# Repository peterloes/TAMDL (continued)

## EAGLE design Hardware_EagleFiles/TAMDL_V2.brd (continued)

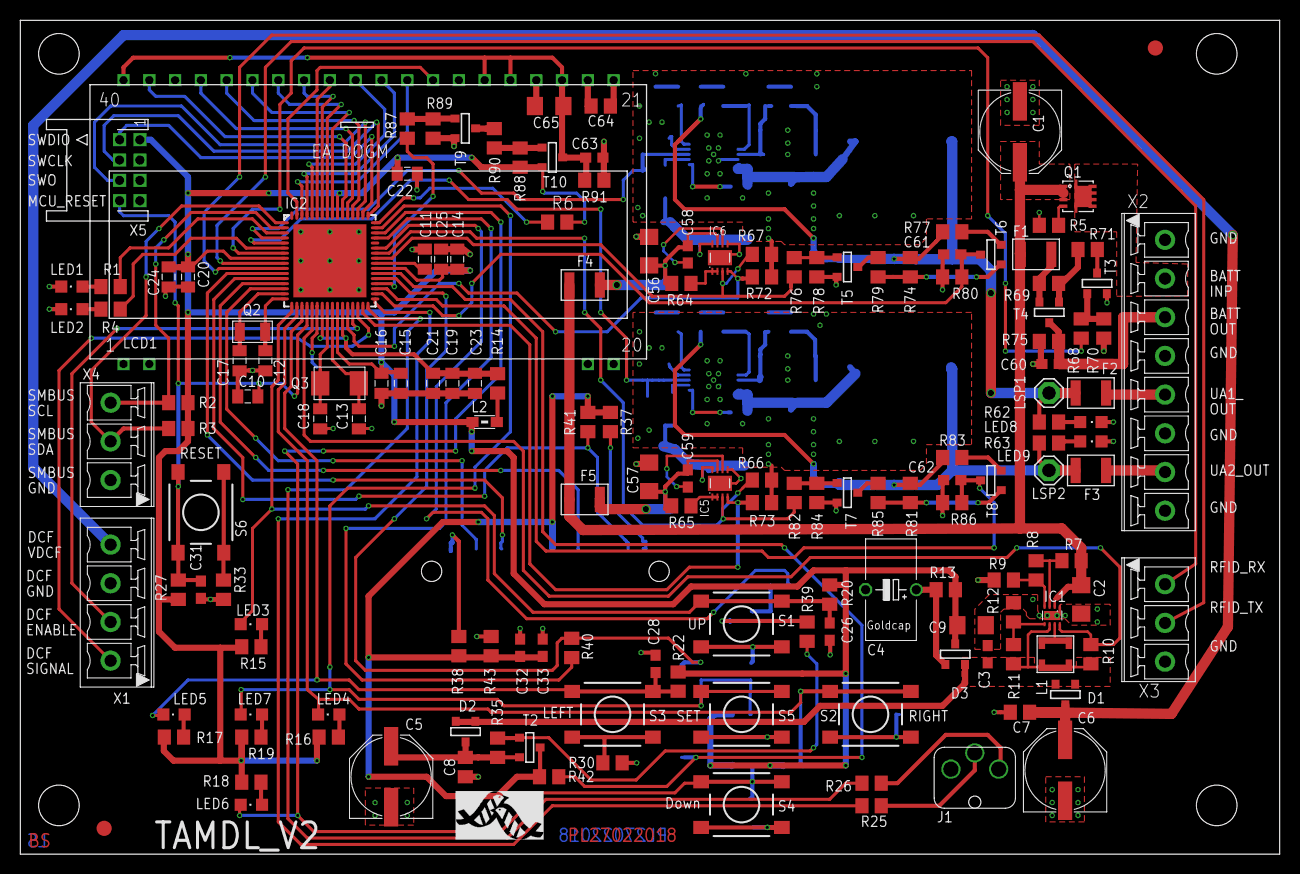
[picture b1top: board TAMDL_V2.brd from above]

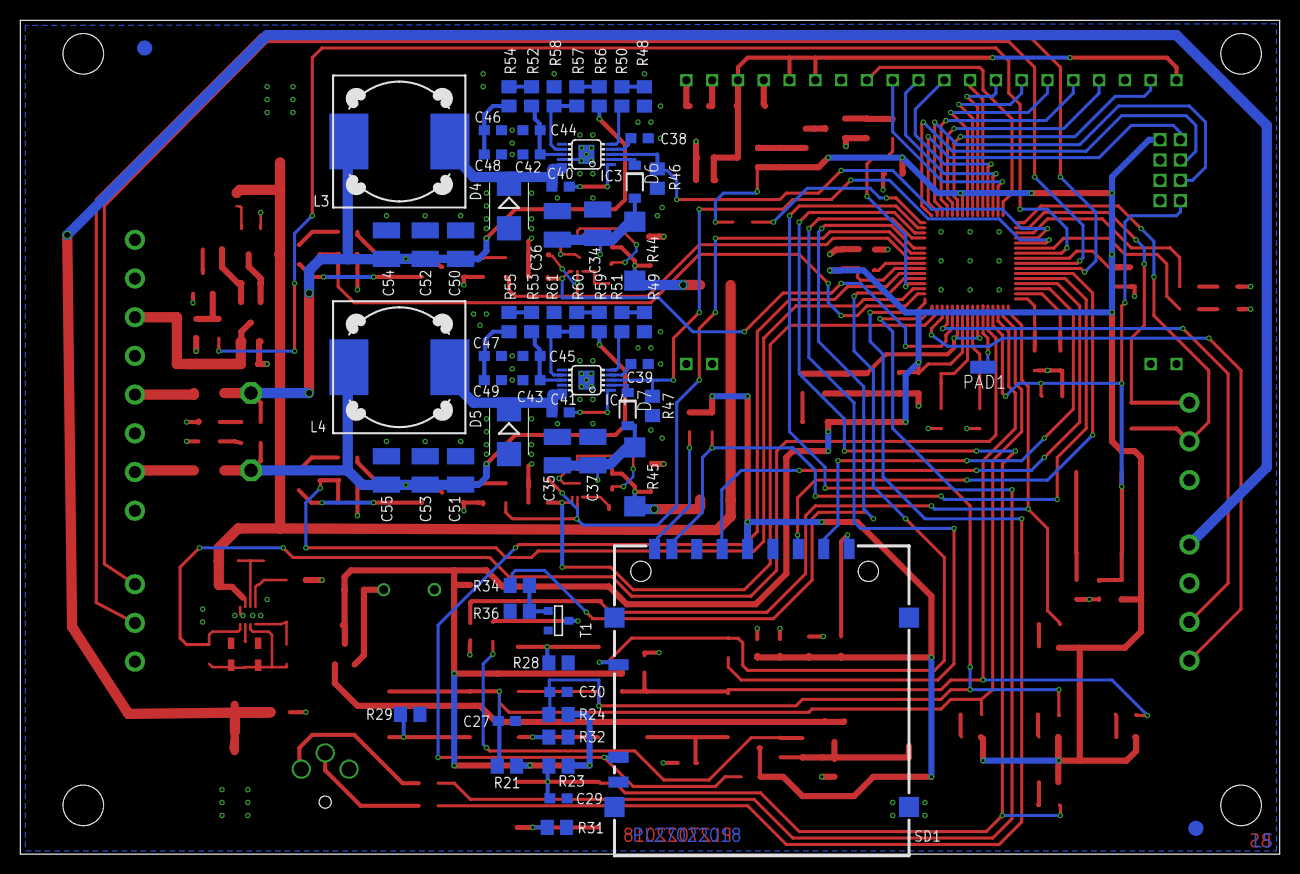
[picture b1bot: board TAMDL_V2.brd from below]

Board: 2 copper layers, 124.0 x 82.1 mm, 222 parts (65 on the bottom side), 148 nets.

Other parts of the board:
U$1: MPIO-ICON

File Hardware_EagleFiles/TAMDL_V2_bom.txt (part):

Part  Value                                             Device                  Package                Description                                                    MPN     OC_FARNELL OC_NEWARK PACKAGE  SUPPLIER         
C1    100µF/25V                                         CPOL-EUE                PANASONIC_E            POLARIZED CAPACITOR, European symbol                                                                                  
C2    10µF/25V                                          C-EUC1206               C1206                  CAPACITOR, European symbol                                                                                            
C3    22µF/10V                                          C-EUC0603               C0603                  CAPACITOR, European symbol                                                                                            
C4    EECS0HD 224;Panasonic                             GOLDCAPSPK-V            GOLDCAPSPK-V                                                                                                                                 
C5    100µF/25V                                         CPOL-EUE                PANASONIC_E            POLARIZED CAPACITOR, European symbol                                                                                  
C6    100µF/25V                                         CPOL-EUE                PANASONIC_E            POLARIZED CAPACITOR, European symbol                                                                                  
C7    100nF/16V                                         C-EUC0805               C0805                  CAPACITOR, European symbol                                                                                            
C8    100nF/16V                                         C-EUC0805               C0805                  CAPACITOR, European symbol                                                                                            
C9    10µ/25V                                           C-EUC1206               C1206                  CAPACITOR, European symbol                                                                                            
C10   100n                                              C_SMD0805               0805                                                                                                                                         
C11   1u                                                C_SMD0805               0805                                                                                                                                         
C12   18p                                               C_SMD0805               0805                                                                                                                                         
C13   12p                                               C_SMD0805               0805                                                                                                                                         
C14   100n                                              C_SMD0805               0805                                                                                                                                         
C15   100n                                              C_SMD0805               0805                                                                                                                                         
C16   100n                                              C_SMD0805               0805                                                                                                                                         
C17   18p                                               C_SMD0805               0805                                                                                                                                         
C18   12p                                               C_SMD0805               0805                                                                                                                                         
C19   10µ                                               C_SMD0805               0805                                                                                                                                         
C20   100n                                              C_SMD0805               0805                                                                                                                                         
C21   100n                                              C_SMD0805               0805                                                                                                                                         
C22   100n                                              C_SMD0805               0805                                                                                                                                         
C23   100n                                              C_SMD0805               0805                                                                                                                                         
C24   100n                                              C_SMD0805               0805                                                                                                                                         
C25   10µ                                               C_SMD0805               0805                                                                                                                                         
C26   10nF                                              C-EUC0603               C0603                  CAPACITOR, European symbol                                                                                            
C27   10nF                                              C-EUC0603               C0603                  CAPACITOR, European symbol                                                                                            
C28   10nF                                              C-EUC0603               C0603                  CAPACITOR, European symbol                                                                                            
C29   10nF                                              C-EUC0603               C0603                  CAPACITOR, European symbol                                                                                            
C30   10nF                                              C-EUC0603               C0603                  CAPACITOR, European symbol                                                                                            
C31   10n                                               C-EUC0603               C0603                  CAPACITOR, European symbol                                                                                            
C32   100nF                                             C-EUC0603               C0603                  CAPACITOR, European symbol                                                                                            
C33   100nF                                             C-EUC0603               C0603                  CAPACITOR, European symbol                                                                                            
C34   4.7µF                                             C-EUC1210               C1210                  CAPACITOR, European symbol                                                                                            
C35   4.7µF                                             C-EUC1210               C1210                  CAPACITOR, European symbol                                                                                            
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
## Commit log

2019-09-30 Update README.md
    Lotte
